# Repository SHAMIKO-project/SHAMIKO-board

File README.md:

# SHAMIKO

**SHAMIKO: an open-source side-channel analysis board with dual Xilinx Spartan-7 FPGAs**

SHAMIKOは、SAKURA-Gと同等の機能を実現することを目標として開発された、電力解析攻撃（サイドチャネル攻撃）の実験用FPGA基板です。Xilinx Spartan-7を搭載しており、ISEではなく最新のVivadoを用いた開発が可能です。

回路図・基板設計データ・プロジェクト固有ライブラリを含むすべての設計データをKiCad形式で公開しており、自由に改変できます。Main FPGA部分を自作ICに置き換えて電力解析を行うといったカスタマイズも可能です。

## Features

- **Dual FPGA構成** — 制御・PC通信用のControl FPGAと、解析対象回路を実装するMain FPGA（いずれもXilinx Spartan-7）
- **Vivado対応** — 最新のVivado / Vitisによる開発が可能
- **電力測定回路** — Main FPGAのコア電源ラインにシャント抵抗を挿入。SAKURA-G同等のオンボードアンプ、またはシャント抵抗両端のBNC端子から直接、オシロスコープで消費電力を観測可能
- **低ノイズ電源設計** — DC-DC + LDOの二段降圧、Control / Main独立の1.0V電源系統
- **柔軟な測定対象切り替え** — 0Ωジャンパ抵抗によりVCC_INTのみ / VCC_INT + VCC_BRAMの測定を選択可能
- **高速PC通信** — FT600（パラレルバス）およびFT2232H（UART / FIFO）を搭載
- **完全オープンソース** — KiCadプロジェクト一式（回路図・基板・ライブラリ）を公開

## Revision Status

| Revision | Status |
|---|---|
| Rev Alpha | 製造済み・評価中 |
| Rev Beta | 設計中（未製造） |
| Rev 1.0 | Rev Betaの動作確認後にリリース予定 |

## Repository Structure

```
SHAMIKO-board/
├── hardware/       # KiCadプロジェクト（回路図・基板・ライブラリ）
├── docs/
│   ├── manual/     # 説明書（LaTeXソース・Markdown）
│   ├── schematic.pdf
│   └── images/
└── LICENSE
```

## Getting Started

### 設計データ

`hardware/` 以下のKiCadプロジェクトから回路図・基板データを閲覧できます。

ガーバーデータおよびBOMは、製造・動作確認が完了し次第公開予定です。それまでに製造したい場合はKiCadから各自出力してください。

### 開発環境

- **FPGA開発**: AMD (Xilinx) Vivado
- **基板設計**: KiCad

### 電源

外部ACアダプタ（12V）から給電します。電源シーケンスは基板上で自動的に制御されます。

## Documentation

詳細な仕様（電源システム、クロック、コンフィグレーション、ピンアサインなど）は説明書を参照してください。

- 説明書PDF: [Releases](https://github.com/SHAMIKO-project/SHAMIKO-board/releases) に添付
- Markdown版: `docs/manual/`

## Sample Designs / Host Software

サンプルHDL（暗号実装例）およびホストPC側の通信ソフトウェアは現在準備中です。Coming soon.

## Contact

- 不具合報告・質問: [GitHub Issues](https://github.com/SHAMIKO-project/SHAMIKO-board/issues)
- Discordコミュニティ: Coming soon

## Developers

- Hirata Haruka
- Ohara Ryotaro

## License

このプロジェクトは [MIT License](LICENSE) の下で公開されています。

## Acknowledgements

- [SAKURA-G](http://satoh.cs.uec.ac.jp/SAKURA/hardware/SAKURA-G.html) — サイドチャネル攻撃評価用FPGA基板の先駆的プロジェクト。SHAMIKOはSAKURAプロジェクトとは無関係の独立したプロジェクトですが、この分野を切り拓いた偉大な仕事に畏敬の念を込めて、設計目標の基準とさせていただきました。

---

*English version: [README.en.md](README.en.md)*

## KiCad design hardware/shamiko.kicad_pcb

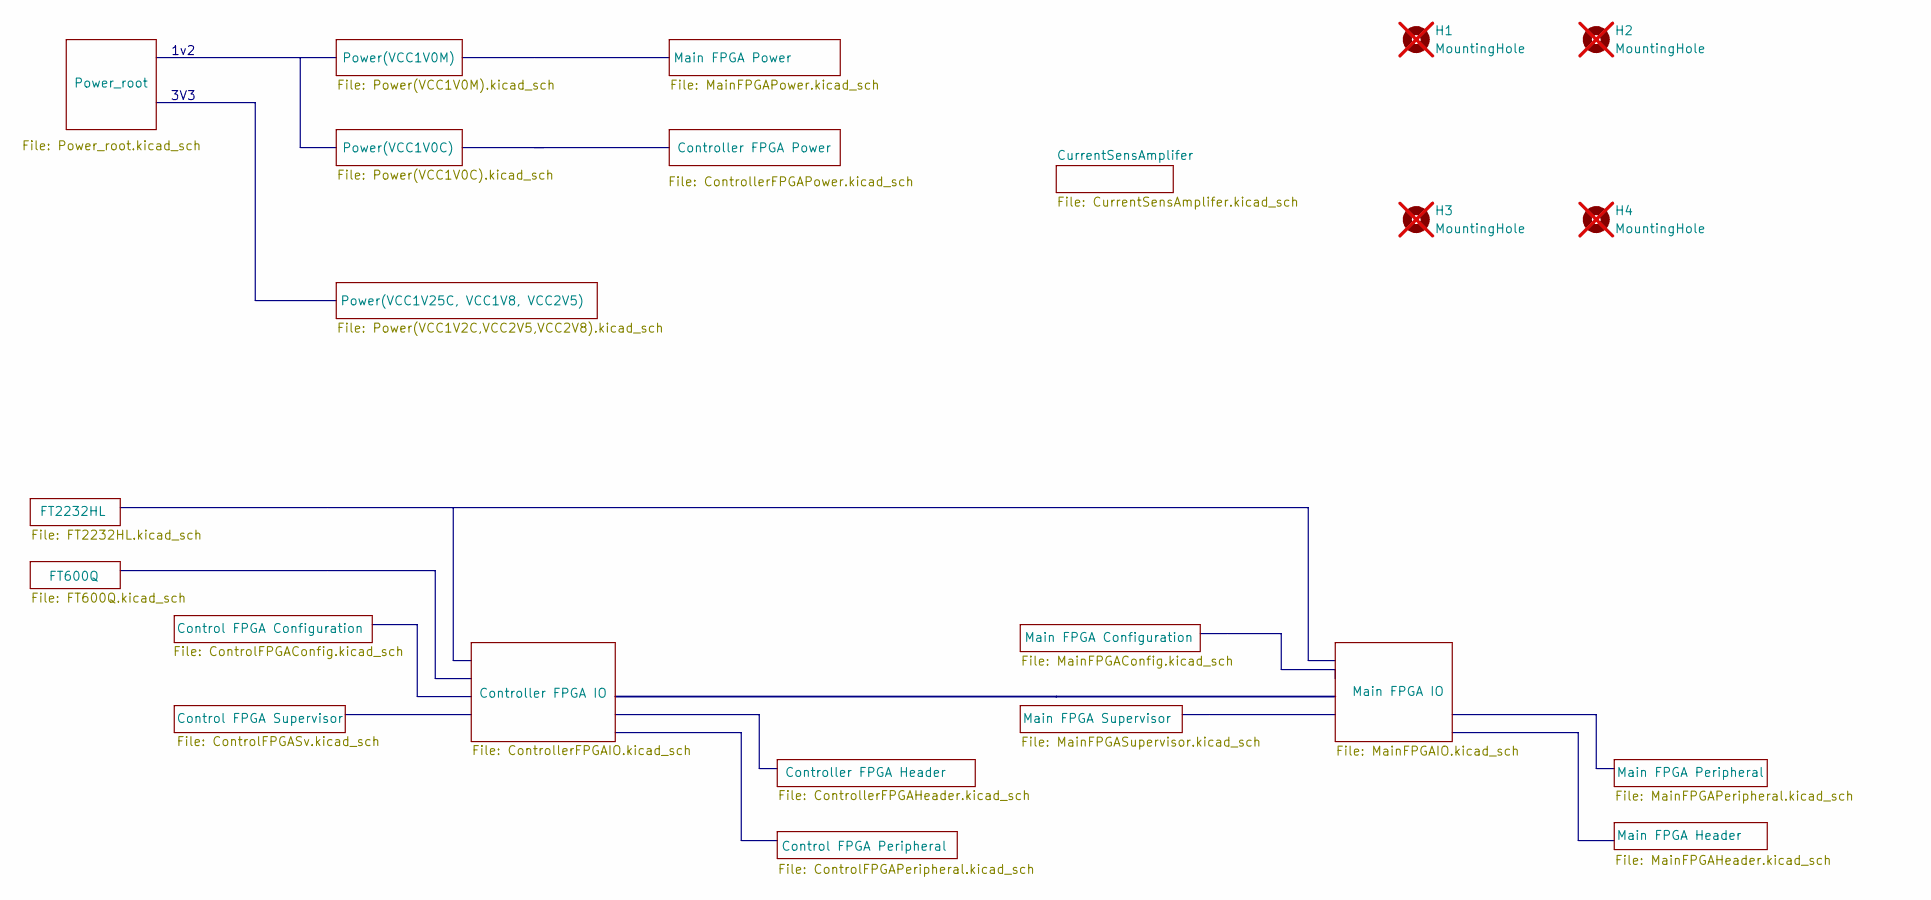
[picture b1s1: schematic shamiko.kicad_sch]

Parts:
H1, H2, H3, H4: MountingHole; MountingHole_3.2mm_M3; not fitted

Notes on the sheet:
3V3
1v2

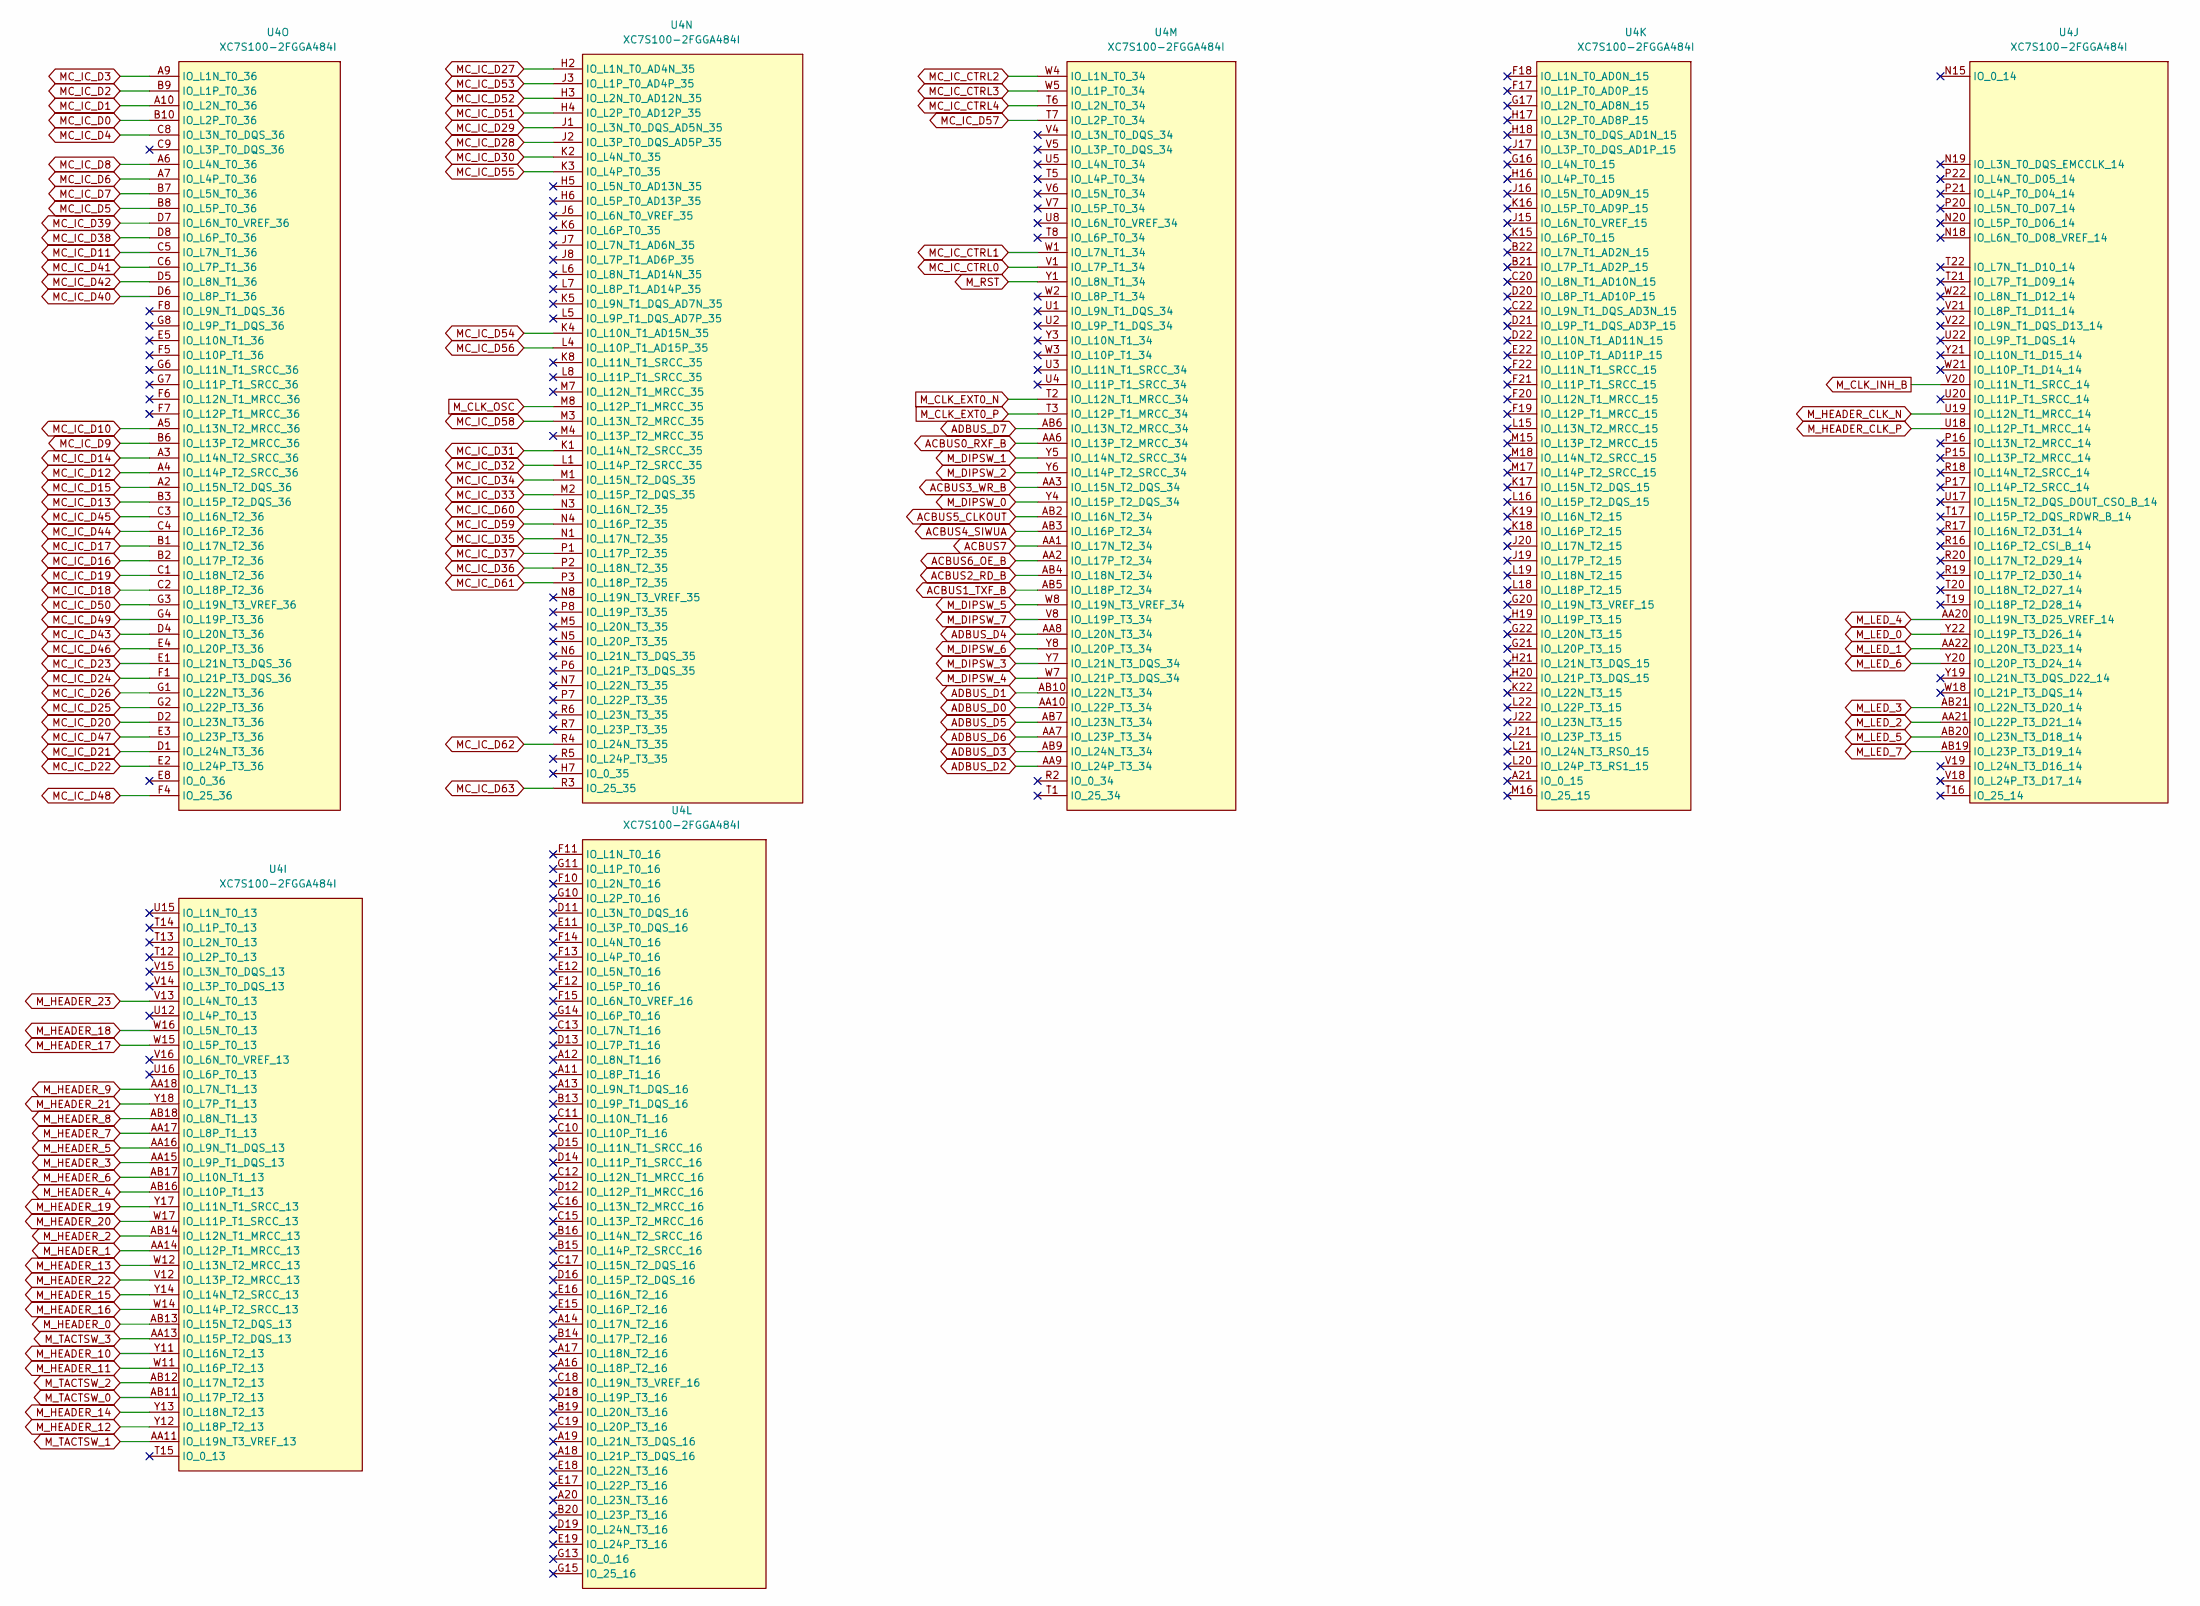
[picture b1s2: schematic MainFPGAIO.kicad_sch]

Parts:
U4: XC7S100-2FGGA484I; Xilinx_FBG484; LCSC C1521770

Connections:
ACBUS0_RXF_B: U4.AA6 (IO_L13P_T2_MRCC_34); also elsewhere on the board
ACBUS1_TXF_B: U4.AB5 (IO_L18P_T2_34); also elsewhere on the board
ACBUS2_RD_B: U4.AB4 (IO_L18N_T2_34); also elsewhere on the board
ACBUS3_WR_B: U4.AA3 (IO_L15N_T2_DQS_34); also elsewhere on the board
ACBUS4_SIWUA: U4.AB3 (IO_L16P_T2_34); also elsewhere on the board
ACBUS5_CLKOUT: U4.AB2 (IO_L16N_T2_34); also elsewhere on the board
ACBUS6_OE_B: U4.AA2 (IO_L17P_T2_34); also elsewhere on the board
ACBUS7: U4.AA1 (IO_L17N_T2_34); also elsewhere on the board
ADBUS_D0: U4.AA10 (IO_L22P_T3_34); also elsewhere on the board
ADBUS_D1: U4.AB10 (IO_L22N_T3_34); also elsewhere on the board
ADBUS_D2: U4.AA9 (IO_L24P_T3_34); also elsewhere on the board
ADBUS_D3: U4.AB9 (IO_L24N_T3_34); also elsewhere on the board
ADBUS_D4: U4.AA8 (IO_L20N_T3_34); also elsewhere on the board
ADBUS_D5: U4.AB7 (IO_L23N_T3_34); also elsewhere on the board
ADBUS_D6: U4.AA7 (IO_L23P_T3_34); also elsewhere on the board
ADBUS_D7: U4.AB6 (IO_L13N_T2_MRCC_34); also elsewhere on the board
MC_IC_CTRL0: U4.V1 (IO_L7P_T1_34); also elsewhere on the board
MC_IC_CTRL1: U4.W1 (IO_L7N_T1_34); also elsewhere on the board
MC_IC_CTRL2: U4.W4 (IO_L1N_T0_34); also elsewhere on the board
MC_IC_CTRL3: U4.W5 (IO_L1P_T0_34); also elsewhere on the board
MC_IC_CTRL4: U4.T6 (IO_L2N_T0_34); also elsewhere on the board
MC_IC_D0: U4.B10 (IO_L2P_T0_36); also elsewhere on the board
MC_IC_D1: U4.A10 (IO_L2N_T0_36); also elsewhere on the board
MC_IC_D2: U4.B9 (IO_L1P_T0_36); also elsewhere on the board
MC_IC_D3: U4.A9 (IO_L1N_T0_36); also elsewhere on the board
MC_IC_D4: U4.C8 (IO_L3N_T0_DQS_36); also elsewhere on the board
MC_IC_D5: U4.B8 (IO_L5P_T0_36); also elsewhere on the board
MC_IC_D6: U4.A7 (IO_L4P_T0_36); also elsewhere on the board
MC_IC_D7: U4.B7 (IO_L5N_T0_36); also elsewhere on the board
MC_IC_D8: U4.A6 (IO_L4N_T0_36); also elsewhere on the board
MC_IC_D9: U4.B6 (IO_L13P_T2_MRCC_36); also elsewhere on the board
MC_IC_D10: U4.A5 (IO_L13N_T2_MRCC_36); also elsewhere on the board
MC_IC_D11: U4.C5 (IO_L7N_T1_36); also elsewhere on the board
MC_IC_D12: U4.A4 (IO_L14P_T2_SRCC_36); also elsewhere on the board
MC_IC_D13: U4.B3 (IO_L15P_T2_DQS_36); also elsewhere on the board
MC_IC_D14: U4.A3 (IO_L14N_T2_SRCC_36); also elsewhere on the board
MC_IC_D15: U4.A2 (IO_L15N_T2_DQS_36); also elsewhere on the board
MC_IC_D16: U4.B2 (IO_L17P_T2_36); also elsewhere on the board
MC_IC_D17: U4.B1 (IO_L17N_T2_36); also elsewhere on the board
MC_IC_D18: U4.C2 (IO_L18P_T2_36); also elsewhere on the board
MC_IC_D19: U4.C1 (IO_L18N_T2_36); also elsewhere on the board
MC_IC_D20: U4.D2 (IO_L23N_T3_36); also elsewhere on the board
MC_IC_D21: U4.D1 (IO_L24N_T3_36); also elsewhere on the board
MC_IC_D22: U4.E2 (IO_L24P_T3_36); also elsewhere on the board
MC_IC_D23: U4.E1 (IO_L21N_T3_DQS_36); also elsewhere on the board
MC_IC_D24: U4.F1 (IO_L21P_T3_DQS_36); also elsewhere on the board
MC_IC_D25: U4.G2 (IO_L22P_T3_36); also elsewhere on the board
MC_IC_D26: U4.G1 (IO_L22N_T3_36); also elsewhere on the board
MC_IC_D27: U4.H2 (IO_L1N_T0_AD4N_35); also elsewhere on the board
MC_IC_D28: U4.J2 (IO_L3P_T0_DQS_AD5P_35); also elsewhere on the board
MC_IC_D29: U4.J1 (IO_L3N_T0_DQS_AD5N_35); also elsewhere on the board
MC_IC_D30: U4.K2 (IO_L4N_T0_35); also elsewhere on the board
MC_IC_D31: U4.K1 (IO_L14N_T2_SRCC_35); also elsewhere on the board
MC_IC_D32: U4.L1 (IO_L14P_T2_SRCC_35); also elsewhere on the board
MC_IC_D33: U4.M2 (IO_L15P_T2_DQS_35); also elsewhere on the board
MC_IC_D34: U4.M1 (IO_L15N_T2_DQS_35); also elsewhere on the board
MC_IC_D35: U4.N1 (IO_L17N_T2_35); also elsewhere on the board
MC_IC_D36: U4.P2 (IO_L18N_T2_35); also elsewhere on the board
MC_IC_D37: U4.P1 (IO_L17P_T2_35); also elsewhere on the board
MC_IC_D38: U4.D8 (IO_L6P_T0_36); also elsewhere on the board
MC_IC_D39: U4.D7 (IO_L6N_T0_VREF_36); also elsewhere on the board
MC_IC_D40: U4.D6 (IO_L8P_T1_36); also elsewhere on the board
MC_IC_D41: U4.C6 (IO_L7P_T1_36); also elsewhere on the board
MC_IC_D42: U4.D5 (IO_L8N_T1_36); also elsewhere on the board
MC_IC_D43: U4.D4 (IO_L20N_T3_36); also elsewhere on the board
MC_IC_D44: U4.C4 (IO_L16P_T2_36); also elsewhere on the board
MC_IC_D45: U4.C3 (IO_L16N_T2_36); also elsewhere on the board
MC_IC_D46: U4.E4 (IO_L20P_T3_36); also elsewhere on the board
MC_IC_D47: U4.E3 (IO_L23P_T3_36); also elsewhere on the board
MC_IC_D48: U4.F4 (IO_25_36); also elsewhere on the board
MC_IC_D49: U4.G4 (IO_L19P_T3_36); also elsewhere on the board
MC_IC_D50: U4.G3 (IO_L19N_T3_VREF_36); also elsewhere on the board
MC_IC_D51: U4.H4 (IO_L2P_T0_AD12P_35); also elsewhere on the board
MC_IC_D52: U4.H3 (IO_L2N_T0_AD12N_35); also elsewhere on the board
MC_IC_D53: U4.J3 (IO_L1P_T0_AD4P_35); also elsewhere on the board
MC_IC_D54: U4.K4 (IO_L10N_T1_AD15N_35); also elsewhere on the board
MC_IC_D55: U4.K3 (IO_L4P_T0_35); also elsewhere on the board
MC_IC_D56: U4.L4 (IO_L10P_T1_AD15P_35); also elsewhere on the board
MC_IC_D57: U4.T7 (IO_L2P_T0_34); also elsewhere on the board
MC_IC_D58: U4.M3 (IO_L13N_T2_MRCC_35); also elsewhere on the board
MC_IC_D59: U4.N4 (IO_L16P_T2_35); also elsewhere on the board
MC_IC_D60: U4.N3 (IO_L16N_T2_35); also elsewhere on the board
MC_IC_D61: U4.P3 (IO_L18P_T2_35); also elsewhere on the board
MC_IC_D62: U4.R4 (IO_L24N_T3_35); also elsewhere on the board
MC_IC_D63: U4.R3 (IO_25_35); also elsewhere on the board
M_CLK_EXT0_N: U4.T2 (IO_L12N_T1_MRCC_34); also elsewhere on the board
M_CLK_EXT0_P: U4.T3 (IO_L12P_T1_MRCC_34); also elsewhere on the board
M_CLK_INH_B: U4.V20 (IO_L11N_T1_SRCC_14); also elsewhere on the board
M_CLK_OSC: U4.M8 (IO_L12P_T1_MRCC_35); also elsewhere on the board
M_DIPSW_0: U4.Y4 (IO_L15P_T2_DQS_34); also elsewhere on the board
M_DIPSW_1: U4.Y5 (IO_L14N_T2_SRCC_34); also elsewhere on the board
M_DIPSW_2: U4.Y6 (IO_L14P_T2_SRCC_34); also elsewhere on the board
M_DIPSW_3: U4.Y7 (IO_L21N_T3_DQS_34); also elsewhere on the board
M_DIPSW_4: U4.W7 (IO_L21P_T3_DQS_34); also elsewhere on the board
M_DIPSW_5: U4.W8 (IO_L19N_T3_VREF_34); also elsewhere on the board
M_DIPSW_6: U4.Y8 (IO_L20P_T3_34); also elsewhere on the board
M_DIPSW_7: U4.V8 (IO_L19P_T3_34); also elsewhere on the board
M_HEADER_0: U4.AB13 (IO_L15N_T2_DQS_13); also elsewhere on the board
M_HEADER_1: U4.AA14 (IO_L12P_T1_MRCC_13); also elsewhere on the board
M_HEADER_2: U4.AB14 (IO_L12N_T1_MRCC_13); also elsewhere on the board
M_HEADER_3: U4.AA15 (IO_L9P_T1_DQS_13); also elsewhere on the board
M_HEADER_4: U4.AB16 (IO_L10P_T1_13); also elsewhere on the board
M_HEADER_5: U4.AA16 (IO_L9N_T1_DQS_13); also elsewhere on the board
M_HEADER_6: U4.AB17 (IO_L10N_T1_13); also elsewhere on the board
M_HEADER_7: U4.AA17 (IO_L8P_T1_13); also elsewhere on the board
M_HEADER_8: U4.AB18 (IO_L8N_T1_13); also elsewhere on the board
M_HEADER_9: U4.AA18 (IO_L7N_T1_13); also elsewhere on the board
M_HEADER_10: U4.Y11 (IO_L16N_T2_13); also elsewhere on the board
M_HEADER_11: U4.W11 (IO_L16P_T2_13); also elsewhere on the board
M_HEADER_12: U4.Y12 (IO_L18P_T2_13); also elsewhere on the board
M_HEADER_13: U4.W12 (IO_L13N_T2_MRCC_13); also elsewhere on the board
M_HEADER_14: U4.Y13 (IO_L18N_T2_13); also elsewhere on the board
M_HEADER_15: U4.Y14 (IO_L14N_T2_SRCC_13); also elsewhere on the board
M_HEADER_16: U4.W14 (IO_L14P_T2_SRCC_13); also elsewhere on the board
M_HEADER_17: U4.W15 (IO_L5P_T0_13); also elsewhere on the board
M_HEADER_18: U4.W16 (IO_L5N_T0_13); also elsewhere on the board
M_HEADER_19: U4.Y17 (IO_L11N_T1_SRCC_13); also elsewhere on the board
M_HEADER_20: U4.W17 (IO_L11P_T1_SRCC_13); also elsewhere on the board
M_HEADER_21: U4.Y18 (IO_L7P_T1_13); also elsewhere on the board
M_HEADER_22: U4.V12 (IO_L13P_T2_MRCC_13); also elsewhere on the board
M_HEADER_23: U4.V13 (IO_L4N_T0_13); also elsewhere on the board
M_HEADER_CLK_N: U4.U19 (IO_L12N_T1_MRCC_14); also elsewhere on the board
M_HEADER_CLK_P: U4.U18 (IO_L12P_T1_MRCC_14); also elsewhere on the board
M_LED_0: U4.Y22 (IO_L19P_T3_D26_14); also elsewhere on the board
M_LED_1: U4.AA22 (IO_L20N_T3_D23_14); also elsewhere on the board
M_LED_2: U4.AA21 (IO_L22P_T3_D21_14); also elsewhere on the board
M_LED_3: U4.AB21 (IO_L22N_T3_D20_14); also elsewhere on the board
M_LED_4: U4.AA20 (IO_L19N_T3_D25_VREF_14); also elsewhere on the board
M_LED_5: U4.AB20 (IO_L23N_T3_D18_14); also elsewhere on the board
M_LED_6: U4.Y20 (IO_L20P_T3_D24_14); also elsewhere on the board
M_LED_7: U4.AB19 (IO_L23P_T3_D19_14); also elsewhere on the board
M_RST: U4.Y1 (IO_L8N_T1_34); also elsewhere on the board
M_TACTSW_0: U4.AB11 (IO_L17P_T2_13); also elsewhere on the board
M_TACTSW_1: U4.AA11 (IO_L19N_T3_VREF_13); also elsewhere on the board
M_TACTSW_2: U4.AB12 (IO_L17N_T2_13); also elsewhere on the board
M_TACTSW_3: U4.AA13 (IO_L15P_T2_DQS_13); also elsewhere on the board

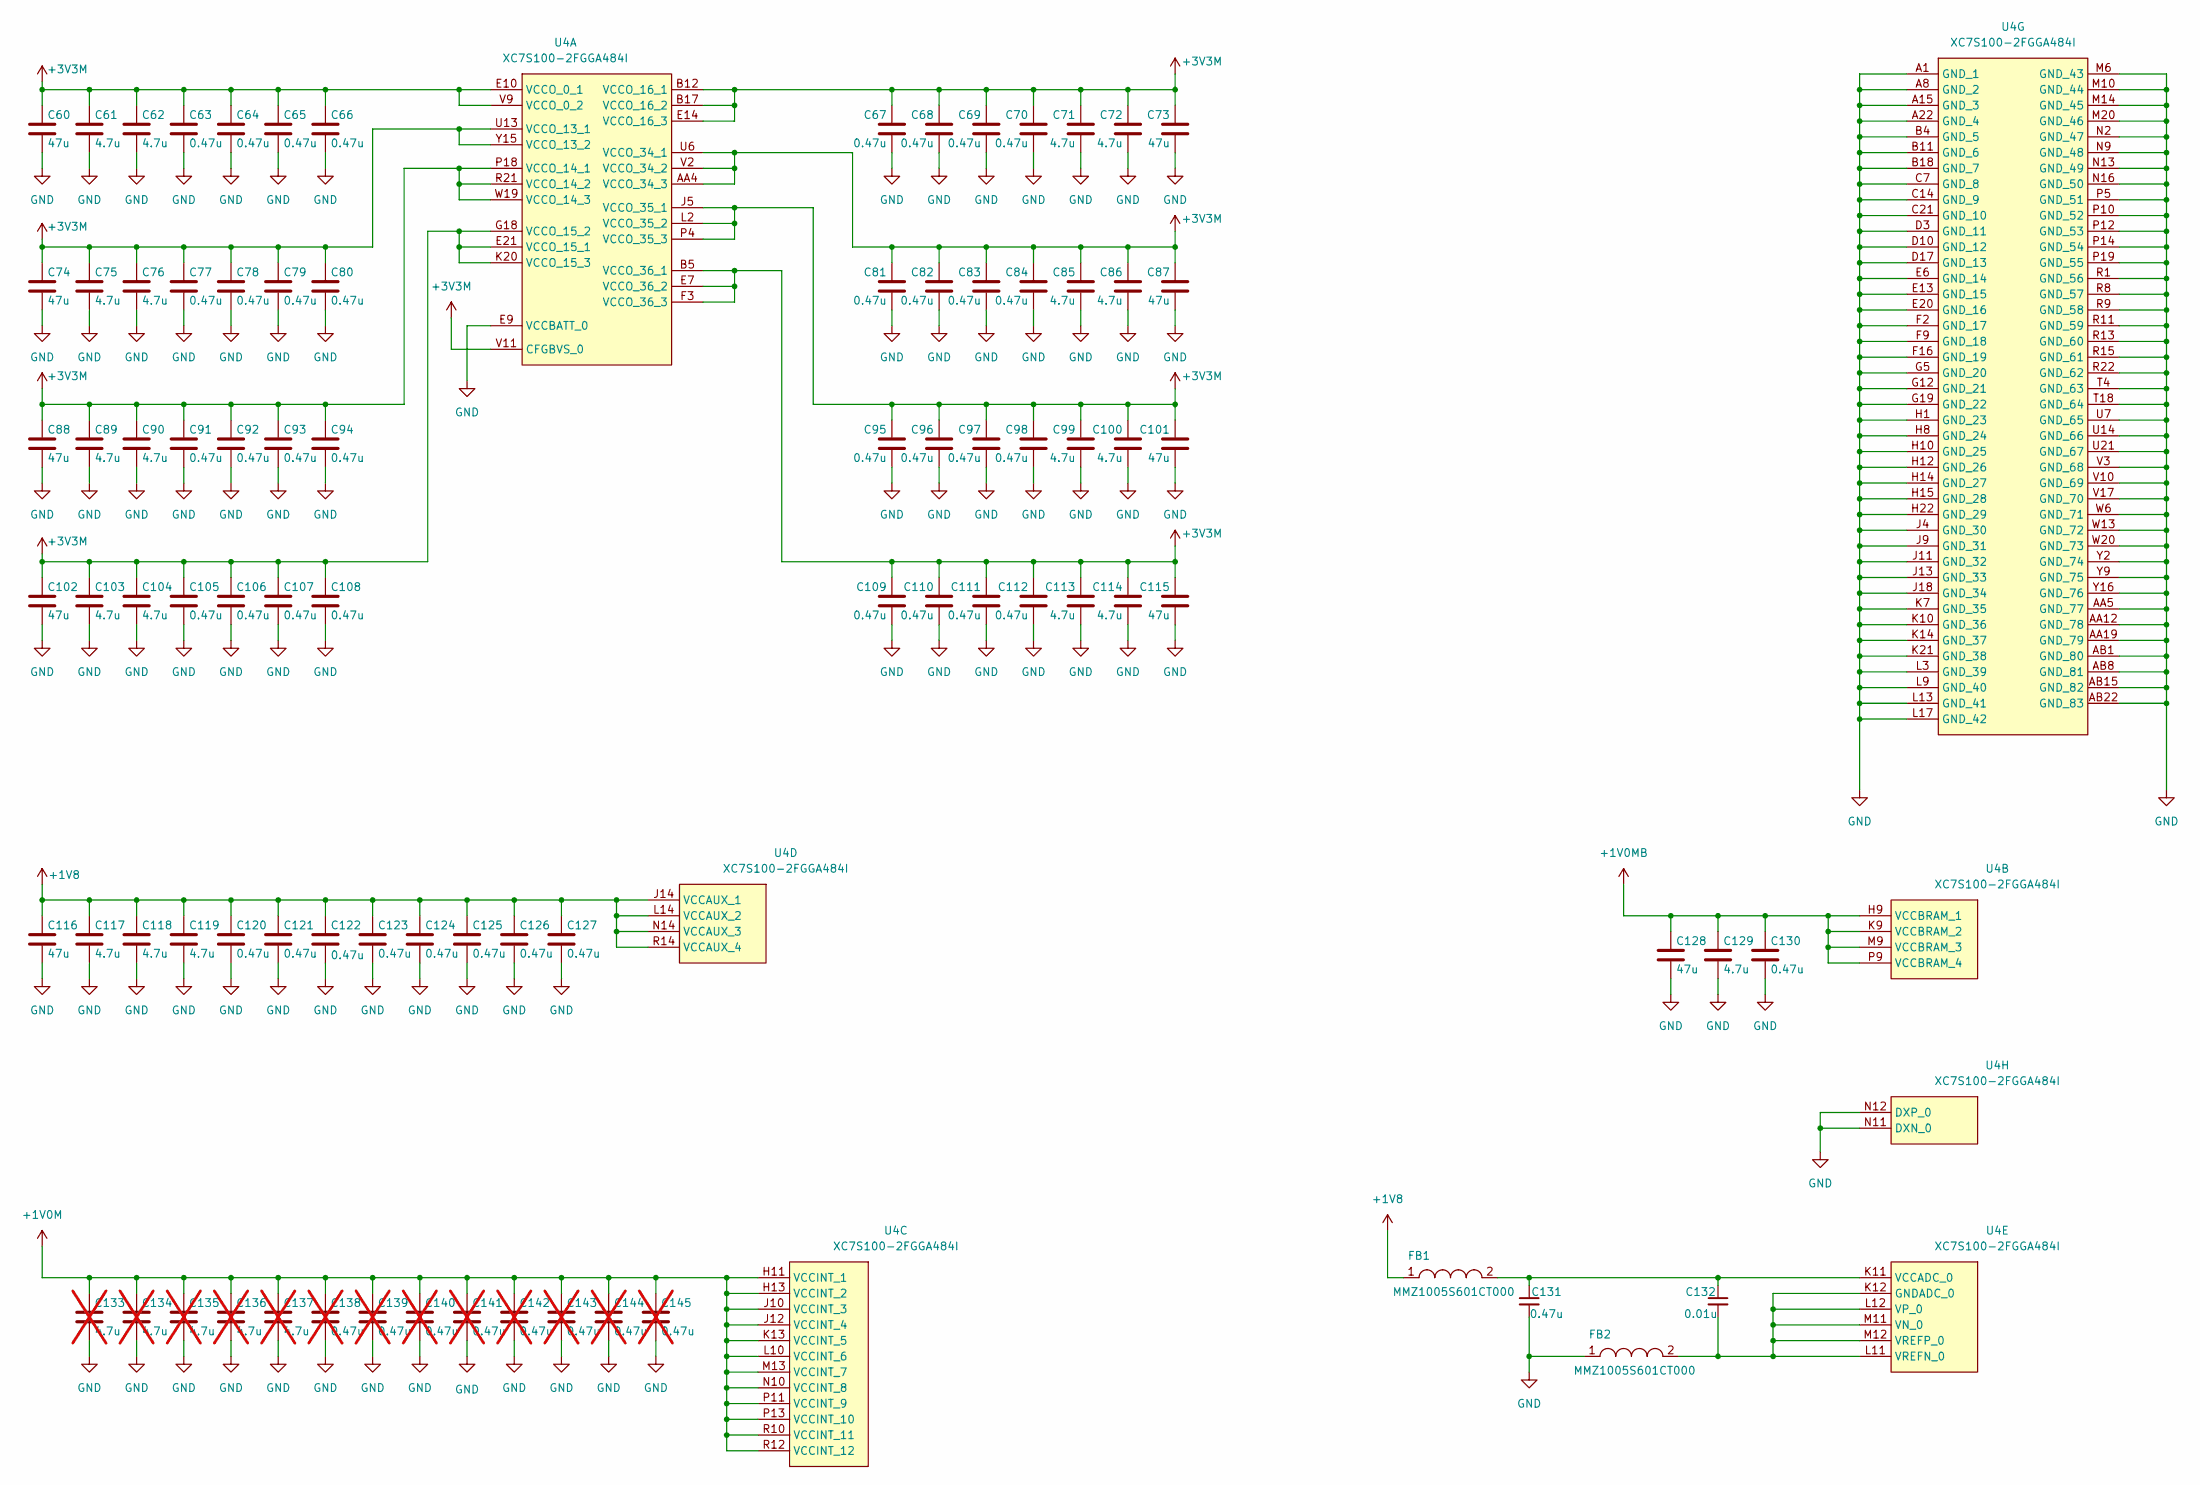
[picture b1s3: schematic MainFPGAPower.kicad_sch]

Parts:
C60, C73, C74, C87, C88, C101, C102, C115, C116, C128: 47u; C_0805_2012Metric; LCSC C124129
C61, C62, C71, C72, C75, C76, C85, C86, C89, C90, C99, C100, C103, C104, C113, C114, C117, C118, C119, C129: 4.7u; C_0603_1608Metric; LCSC C90057
C63, C64, C65, C66, C67, C68, C69, C70, C77, C78, C79, C80, C81, C82, C83, C84, C91, C92, C93, C94, C95, C96, C97, C98, C105, C106, C107, C108, C130, C131: 0.47u; C_0402_1005Metric; LCSC C77003
C109, C110, C111, C112, C120, C121, C122, C123, C124, C125, C126, C127: 0.47u; C_0402_1005Metric_Pad0.74x0.62mm_HandSolder; LCSC C77003
C132: 0.01u; C_0402_1005Metric; LCSC C15195
C133, C134, C135, C136, C137: 4.7u; C_0603_1608Metric_Pad1.08x0.95mm_HandSolder; LCSC C90057; not fitted
C138, C139, C140, C141, C142, C143, C144, C145: 0.47u; C_0402_1005Metric_Pad0.74x0.62mm_HandSolder; LCSC C77003; not fitted
FB1, FB2: MMZ1005S601CT000; LCSC C76804
U4: XC7S100-2FGGA484I; Xilinx_FBG484; LCSC C1521770

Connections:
+1V0M: C133.1, C134.1, C135.1, C136.1, C137.1, C138.1, C139.1, C140.1, C141.1, C142.1, C143.1, C144.1, C145.1, U4.H11 (VCCINT_1), U4.H13 (VCCINT_2), U4.J10 (VCCINT_3), U4.J12 (VCCINT_4), U4.K13 (VCCINT_5), U4.L10 (VCCINT_6), U4.M13 (VCCINT_7), U4.N10 (VCCINT_8), U4.P11 (VCCINT_9), U4.P13 (VCCINT_10), U4.R10 (VCCINT_11), U4.R12 (VCCINT_12); also elsewhere on the board
+1V0MB: C128.1, C129.1, C130.1, U4.H9 (VCCBRAM_1), U4.K9 (VCCBRAM_2), U4.M9 (VCCBRAM_3), U4.P9 (VCCBRAM_4); also elsewhere on the board
+1V8: C116.1, C117.1, C118.1, C119.1, C120.1, C121.1, C122.1, C123.1, C124.1, C125.1, C126.1, C127.1, FB1.1, U4.J14 (VCCAUX_1), U4.L14 (VCCAUX_2), U4.N14 (VCCAUX_3), U4.R14 (VCCAUX_4); also elsewhere on the board
+3V3M: C60.1, C61.1, C62.1, C63.1, C64.1, C65.1, C66.1, C67.1, C68.1, C69.1, C70.1, C71.1, C72.1, C73.1, C74.1, C75.1, C76.1, C77.1, C78.1, C79.1, C80.1, C81.1, C82.1, C83.1, C84.1, C85.1, C86.1, C87.1, C88.1, C89.1, C90.1, C91.1, C92.1, C93.1, C94.1, C95.1, C96.1, C97.1, C98.1, C99.1, C100.1, C101.1, C102.1, C103.1, C104.1, C105.1, C106.1, C107.1, C108.1, C109.1, C110.1, C111.1, C112.1, C113.1, C114.1, C115.1, U4.AA4 (VCCO_34_3), U4.B5 (VCCO_36_1), U4.B12 (VCCO_16_1), U4.B17 (VCCO_16_2), U4.E7 (VCCO_36_2), U4.E10 (VCCO_0_1), U4.E14 (VCCO_16_3), U4.E21 (VCCO_15_1), U4.F3 (VCCO_36_3), U4.G18 (VCCO_15_2), U4.J5 (VCCO_35_1), U4.K20 (VCCO_15_3), U4.L2 (VCCO_35_2), U4.P4 (VCCO_35_3), U4.P18 (VCCO_14_1), U4.R21 (VCCO_14_2), U4.U6 (VCCO_34_1), U4.U13 (VCCO_13_1), U4.V2 (VCCO_34_2), U4.V9 (VCCO_0_2), U4.V11 (CFGBVS_0), U4.W19 (VCCO_14_3), U4.Y15 (VCCO_13_2); also elsewhere on the board
GND: C60.2, C61.2, C62.2, C63.2, C64.2, C65.2, C66.2, C67.2, C68.2, C69.2, C70.2, C71.2, C72.2, C73.2, C74.2, C75.2, C76.2, C77.2, C78.2, C79.2, C80.2, C81.2, C82.2, C83.2, C84.2, C85.2, C86.2, C87.2, C88.2, C89.2, C90.2, C91.2, C92.2, C93.2, C94.2, C95.2, C96.2, C97.2, C98.2, C99.2, C100.2, C101.2, C102.2, C103.2, C104.2, C105.2, C106.2, C107.2, C108.2, C109.2, C110.2, C111.2, C112.2, C113.2, C114.2, C115.2, C116.2, C117.2, C118.2, C119.2, C120.2, C121.2, C122.2, C123.2, C124.2, C125.2, C126.2, C127.2, C128.2, C129.2, C130.2, C131.2, C133.2, C134.2, C135.2, C136.2, C137.2, C138.2, C139.2, C140.2, C141.2, C142.2, C143.2, C144.2, C145.2, FB2.1, U4.A1 (GND_1), U4.A8 (GND_2), U4.A15 (GND_3), U4.A22 (GND_4), U4.AA5 (GND_77), U4.AA12 (GND_78), U4.AA19 (GND_79), U4.AB1 (GND_80), U4.AB8 (GND_81), U4.AB15 (GND_82), U4.AB22 (GND_83), U4.B4 (GND_5), U4.B11 (GND_6), U4.B18 (GND_7), U4.C7 (GND_8), U4.C14 (GND_9), U4.C21 (GND_10), U4.D3 (GND_11), U4.D10 (GND_12), U4.D17 (GND_13), U4.E6 (GND_14), U4.E9 (VCCBATT_0), U4.E13 (GND_15), U4.E20 (GND_16), U4.F2 (GND_17), U4.F9 (GND_18), U4.F16 (GND_19), U4.G5 (GND_20), U4.G12 (GND_21), U4.G19 (GND_22), U4.H1 (GND_23), U4.H8 (GND_24), U4.H10 (GND_25), U4.H12 (GND_26), U4.H14 (GND_27), U4.H15 (GND_28), U4.H22 (GND_29), U4.J4 (GND_30), U4.J9 (GND_31), U4.J11 (GND_32), U4.J13 (GND_33), U4.J18 (GND_34), U4.K7 (GND_35), U4.K10 (GND_36), U4.K14 (GND_37), U4.K21 (GND_38), U4.L3 (GND_39), U4.L9 (GND_40), U4.L13 (GND_41), U4.L17 (GND_42), U4.M6 (GND_43), U4.M10 (GND_44), U4.M14 (GND_45), U4.M20 (GND_46), U4.N2 (GND_47), U4.N9 (GND_48), U4.N11 (DXN_0), U4.N12 (DXP_0), U4.N13 (GND_49), U4.N16 (GND_50), U4.P5 (GND_51), U4.P10 (GND_52), U4.P12 (GND_53), U4.P14 (GND_54), U4.P19 (GND_55), U4.R1 (GND_56), U4.R8 (GND_57), U4.R9 (GND_58), U4.R11 (GND_59), U4.R13 (GND_60), U4.R15 (GND_61), U4.R22 (GND_62), U4.T4 (GND_63), U4.T18 (GND_64), U4.U7 (GND_65), U4.U14 (GND_66), U4.U21 (GND_67), U4.V3 (GND_68), U4.V10 (GND_69), U4.V17 (GND_70), U4.W6 (GND_71), U4.W13 (GND_72), U4.W20 (GND_73), U4.Y2 (GND_74), U4.Y9 (GND_75), U4.Y16 (GND_76); also elsewhere on the board
unnamed: C132.2, FB2.2, U4.K12 (GNDADC_0), U4.L11 (VREFN_0), U4.L12 (VP_0), U4.M11 (VN_0), U4.M12 (VREFP_0)
unnamed: C131.1, C132.1, FB1.2, U4.K11 (VCCADC_0)

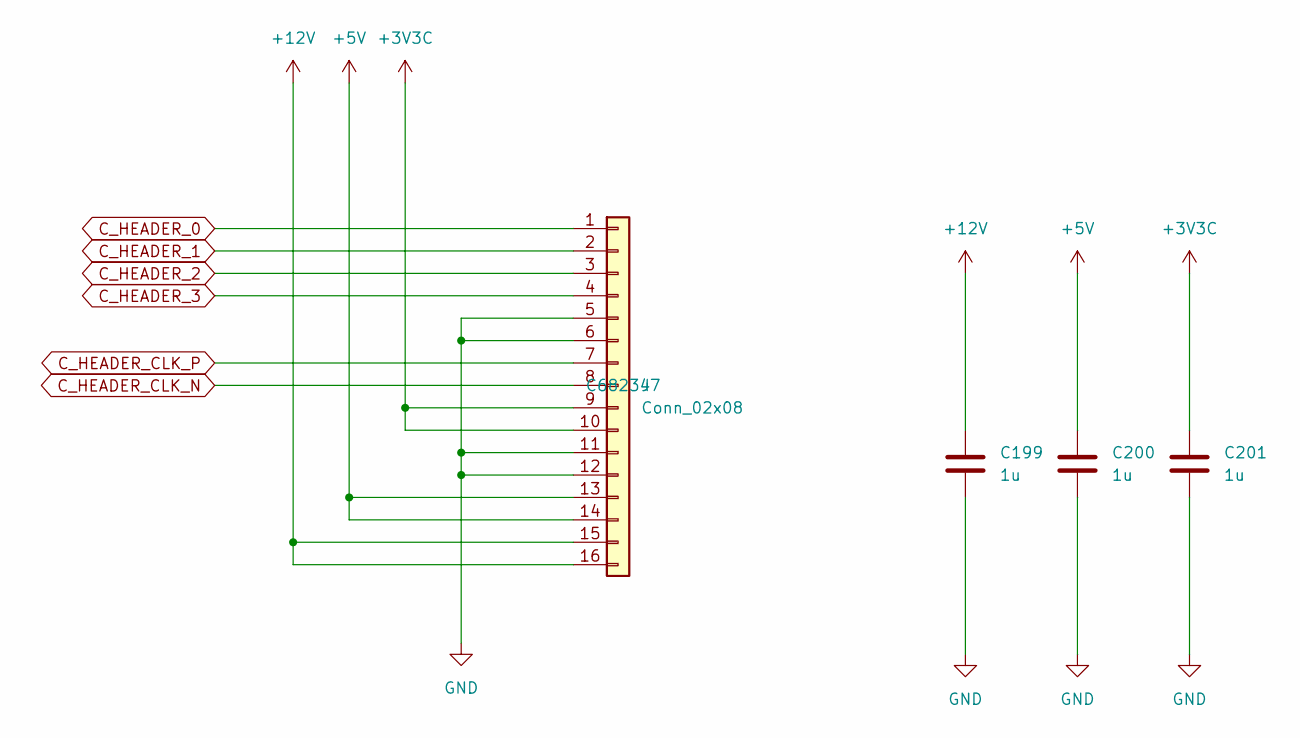
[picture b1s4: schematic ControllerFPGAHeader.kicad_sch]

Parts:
C199: 1u; C_0805_2012Metric; LCSC C126592
C200, C201: 1u; C_0603_1608Metric; LCSC C77386
J7: Conn_02x08; LCSC C68234

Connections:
+3V3C: C201.1, J7.9, J7.10; also elsewhere on the board
+5V: C200.1, J7.13, J7.14; also elsewhere on the board
+12V: C199.1, J7.15, J7.16; also elsewhere on the board
C_HEADER_0: J7.1; also elsewhere on the board
C_HEADER_1: J7.2; also elsewhere on the board
C_HEADER_2: J7.3; also elsewhere on the board
C_HEADER_3: J7.4; also elsewhere on the board
C_HEADER_CLK_N: J7.8; also elsewhere on the board
C_HEADER_CLK_P: J7.7; also elsewhere on the board
GND: C199.2, C200.2, C201.2, J7.5, J7.6, J7.11, J7.12; also elsewhere on the board

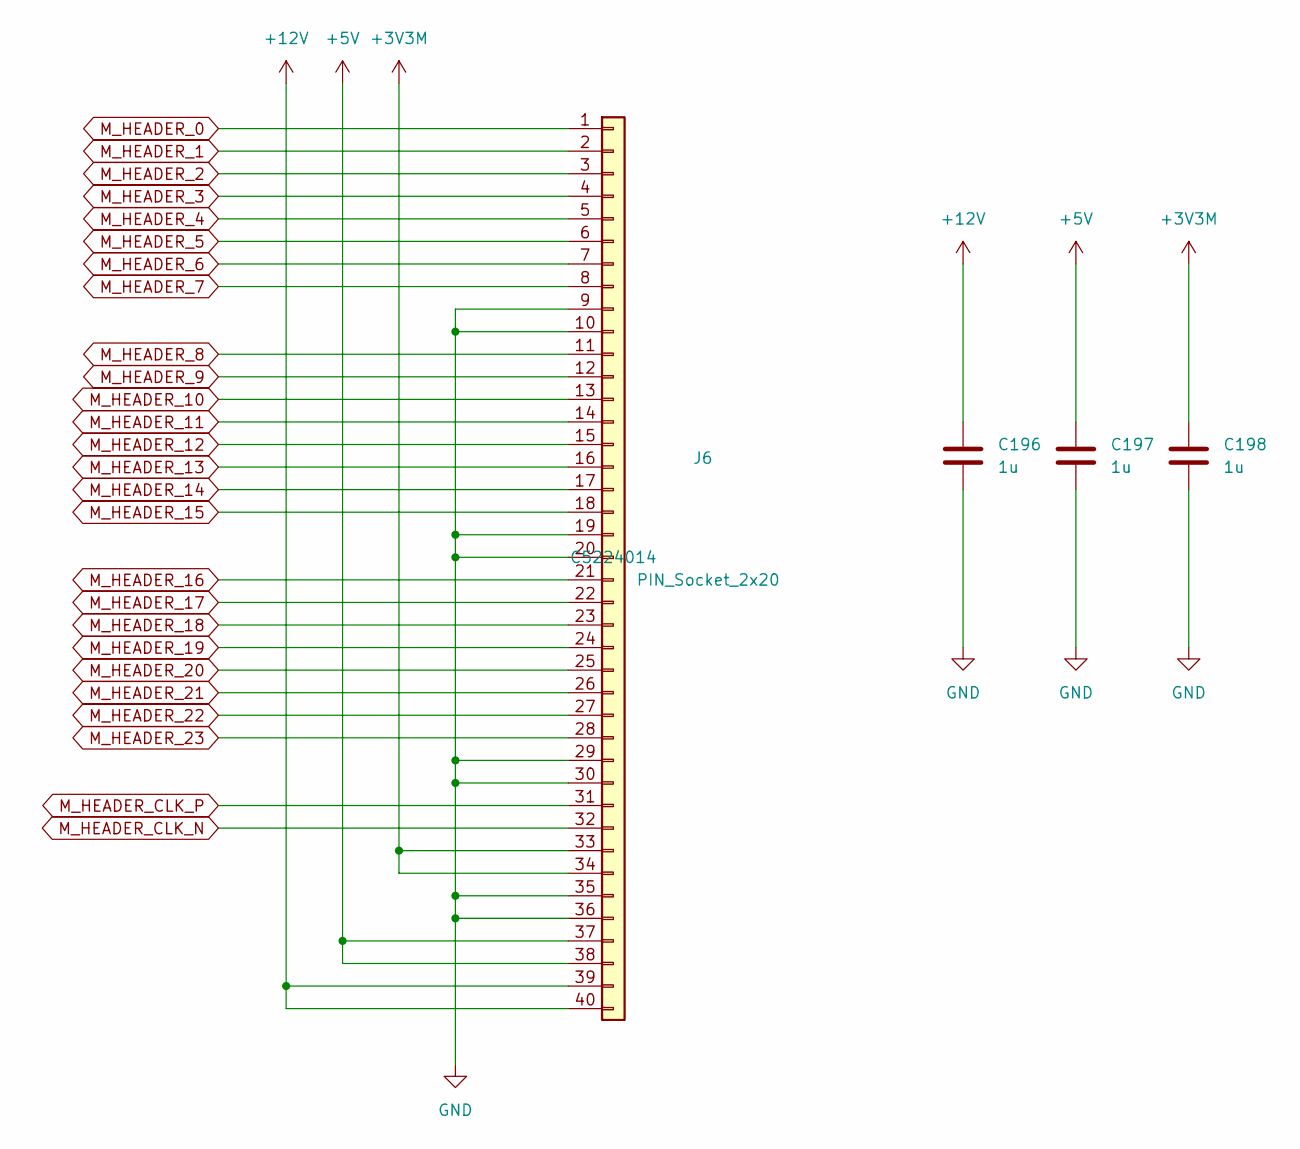
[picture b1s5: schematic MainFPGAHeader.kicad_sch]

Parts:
C196: 1u; C_0805_2012Metric; LCSC C126592
C197, C198: 1u; C_0603_1608Metric; LCSC C77386
J6: PIN_Socket_2x20; ZHOURI PZ2.54-2_20; LCSC C5224014

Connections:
+3V3M: C198.1, J6.33, J6.34; also elsewhere on the board
+5V: C197.1, J6.37, J6.38; also elsewhere on the board
+12V: C196.1, J6.39, J6.40; also elsewhere on the board
GND: C196.2, C197.2, C198.2, J6.9, J6.10, J6.19, J6.20, J6.29, J6.30, J6.35, J6.36; also elsewhere on the board
M_HEADER_0: J6.1; also elsewhere on the board
M_HEADER_1: J6.2; also elsewhere on the board
M_HEADER_2: J6.3; also elsewhere on the board
M_HEADER_3: J6.4; also elsewhere on the board
M_HEADER_4: J6.5; also elsewhere on the board
M_HEADER_5: J6.6; also elsewhere on the board
M_HEADER_6: J6.7; also elsewhere on the board
M_HEADER_7: J6.8; also elsewhere on the board
M_HEADER_8: J6.11; also elsewhere on the board
M_HEADER_9: J6.12; also elsewhere on the board
M_HEADER_10: J6.13; also elsewhere on the board
M_HEADER_11: J6.14; also elsewhere on the board
M_HEADER_12: J6.15; also elsewhere on the board
M_HEADER_13: J6.16; also elsewhere on the board
M_HEADER_14: J6.17; also elsewhere on the board
M_HEADER_15: J6.18; also elsewhere on the board
M_HEADER_16: J6.21; also elsewhere on the board
M_HEADER_17: J6.22; also elsewhere on the board
M_HEADER_18: J6.23; also elsewhere on the board
M_HEADER_19: J6.24; also elsewhere on the board
M_HEADER_20: J6.25; also elsewhere on the board
M_HEADER_21: J6.26; also elsewhere on the board
M_HEADER_22: J6.27; also elsewhere on the board
M_HEADER_23: J6.28; also elsewhere on the board
M_HEADER_CLK_N: J6.32; also elsewhere on the board
M_HEADER_CLK_P: J6.31; also elsewhere on the board
